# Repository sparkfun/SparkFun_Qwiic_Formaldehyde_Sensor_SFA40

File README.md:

The [SparkFun Formaldehyde Sensor - SFA40 (Qwiic)](https://www.sparkfun.com/sparkfun-formaldehyde-sensor-sfa40.html) is a compact indoor air quality breakout built around the SFA40 from Sensirion.
The SFA40 is an electrochemical sensor that measures formaldehyde (HCHO) from 0 to 2000 ppb, with very low cross-sensitivity 
to common indoor gases like ethanol. It is factory-calibrated and outputs concentration directly over I2C, and an onboard 
humidity and temperature sensor compensates the reading automatically. We've wired it to Qwiic connectors so you can read 
calibrated formaldehyde levels with no soldering.

**Note:** The SFA40 needs about 10 minutes after power-on to reach full accuracy, and a status flag in each reading tells you when it is within spec.

## Repository Contents

* **/docs** - Documentation files for GitHub pages
* **/Documents** - Datasheets, additional product information
* **/Hardware** - KiCad design files (.kicad_sch, .kicad_pcb)
* **/Production** - Production panel files

## Documentation

* **[Library](https://github.com/sparkfun/SparkFun_SFA40_Arduino_Library)** - Arduino library for the SparkFun Qwiic Formaldehyde Sensor - SFA40.
* **[Hookup Guide](https://docs.sparkfun.com/SparkFun_Qwiic_Formaldehyde_Sensor_SFA40/)** - Basic hookup guide for the SparkFun Qwiic Formaldehyde Sensor - SFA40.

## Product Versions

* **[SEN-31669](https://www.sparkfun.com/sparkfun-formaldehyde-sensor-sfa40.html)** - Initial release of the SparkFun Qwiic Formaldehyde Sensor - SFA40.

## License Information

This product is _**open source**_!

Please review the LICENSE.md file for license information.

If you have any questions or concerns about licensing, please contact technical support on our [SparkFun forums](https://forum.sparkfun.com/viewforum.php?f=152).

Distributed as-is; no warranty is given.

_- Your friends at SparkFun._

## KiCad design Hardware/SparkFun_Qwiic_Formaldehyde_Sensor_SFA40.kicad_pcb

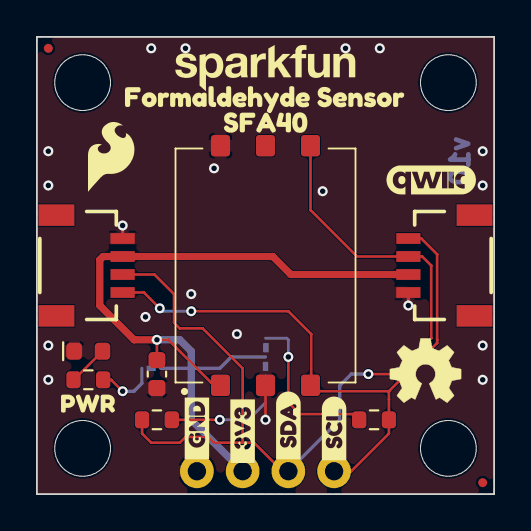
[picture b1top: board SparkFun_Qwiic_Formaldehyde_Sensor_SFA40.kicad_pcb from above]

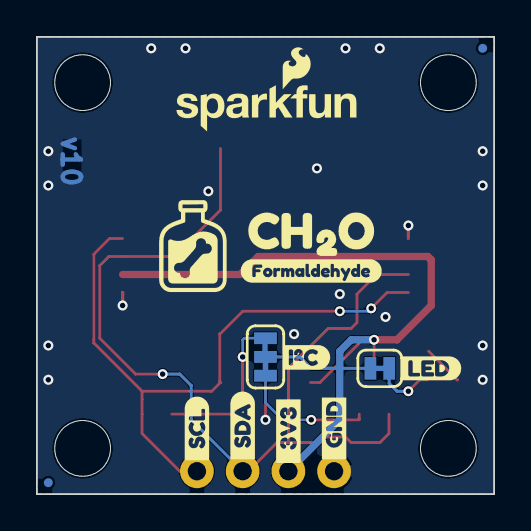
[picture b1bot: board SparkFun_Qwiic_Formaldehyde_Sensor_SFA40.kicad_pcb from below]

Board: 2 copper layers, 25.4 x 25.4 mm, 37 parts (13 on the bottom side), 8 nets.

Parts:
C5: 0.1uF; C_0603_1608Metric
D1: Red; LED_0603_1608Metric_Red
FID1, FID2, FID3, FID4: Fiducial_0.5mm; Fiducial_0.5mm_Mask1mm
G4: OSHW_Logo; Creative_Commons_License
J1, J2: Qwiic_RA; JST_1x04_P1.0mm_Horizontal_SMD
J3: Conn_01x06; 1x04_P2.54mm
JP1: LED; Jumper_2_NC_Trace
JP2: I²C; Jumper_3_NC-2_Trace
R3: 4.7k; R_0603_1608Metric
R4, R5: 2.2k; R_0603_1608Metric
Ref**: Val**; OSHW_Logo_4mm
ST1, ST2, ST3, ST4: Standoff
U3: SFA40
kibuzzard-6A0365C6: G***; kibuzzard-6A0365C6
kibuzzard-6A23318A: G***; kibuzzard-6A23318A
kibuzzard-6A23378A: G***; kibuzzard-6A23378A
kibuzzard-6A172007: G***; kibuzzard-6A172007
kibuzzard-6A233140: G***; kibuzzard-6A233140
kibuzzard-6A233190: G***; kibuzzard-6A233190
kibuzzard-6A233774: G***; kibuzzard-6A233774
kibuzzard-6A233784: G***; kibuzzard-6A233784
kibuzzard-689A66E2: G***; kibuzzard-689A66E2
kibuzzard-689A66EE: G***; kibuzzard-689A66EE
kibuzzard-689A66F4: G***; kibuzzard-689A66F4
kibuzzard-689A642E: G***; kibuzzard-689A642E
kibuzzard-689A6711: G***; kibuzzard-689A6711
kibuzzard-689A6718: G***; kibuzzard-689A6718
kibuzzard-689A6728: G***; kibuzzard-689A6728
kibuzzard-689A6796: G***; kibuzzard-689A6796

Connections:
3.3V: C5.1, J1.2, J2.2, J3.2, JP1.2 (B), JP2.2 (B), U3.1 (VDD)
GND: C5.2, D1.1 (K), J1.1, J2.1, J3.1, U3.2 (GND), U3.6 (GND)
unnamed: D1.2 (A), R3.1
unnamed: JP1.1 (A), R3.2
unnamed: JP2.1 (A), R5.2
unnamed: JP2.3 (C), R4.2
SCL: J1.4, J2.4, J3.4, R4.1, U3.3 (SCL)
SDA: J1.3, J2.3, J3.3, R5.1, U3.4 (SDA)

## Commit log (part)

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2026-06-09 Design Review Changes
2026-06-09 Rolls version to v10

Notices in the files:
parts and their libraries:
Released under the Creative Commons Attribution Share-Alike 4.0 License
https://creativecommons.org/licenses/by-sa/4.0
